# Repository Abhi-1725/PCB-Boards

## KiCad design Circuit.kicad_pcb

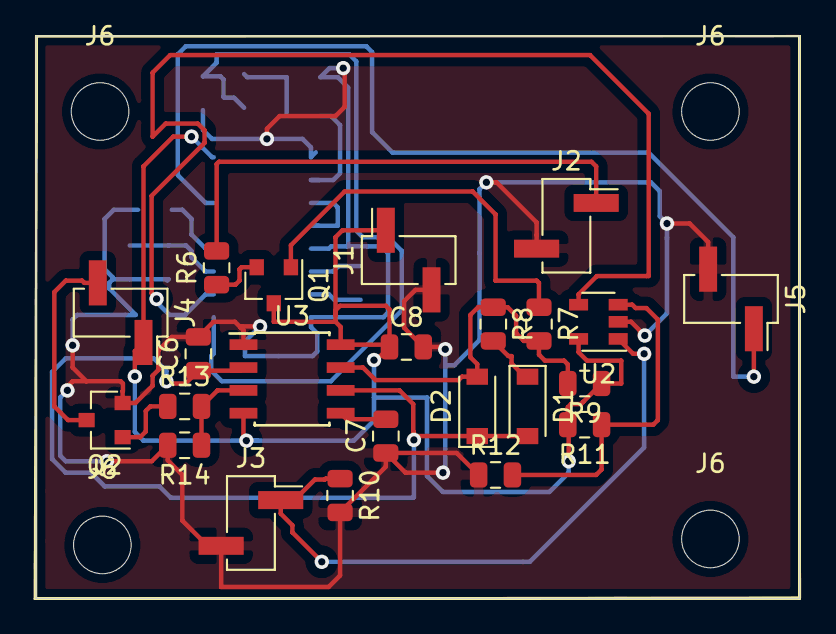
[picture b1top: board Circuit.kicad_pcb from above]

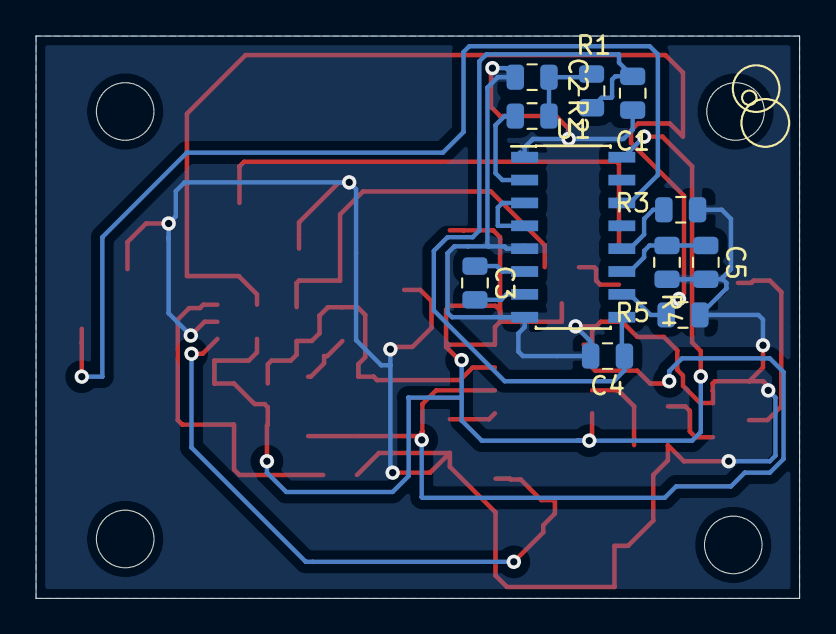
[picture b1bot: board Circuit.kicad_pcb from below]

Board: 2 copper layers, 42.4 x 31.2 mm, 38 parts (11 on the bottom side), 25 nets.

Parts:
C1: 100nF; C_0805_2012Metric
C2: 10nF; C_0805_2012Metric
C3: 22nF; C_0805_2012Metric
C4: 4.7nF; C_0805_2012Metric
C5: 2.2nF; C_0805_2012Metric
C6: 15nF; C_0805_2012Metric
C7: 1nF; C_0805_2012Metric
C8: 2200uF; C_0805_2012Metric
D1, D2: D; D_SOD-123
J1, J2, J3, J4, J5: T; PinHeader_1x02_P2.54mm_Vertical_SMD_Pin1Right
J6, J6#2, J6#3, J6#4: Conn_01x01_Male; MountingHole_3.2mm_M3
Q1: BC327; SOT-23
Q2: 2N7002E; SOT-23
R1, R2, R8: 1K; R_0805_2012Metric
R3, R4: 15K; R_0805_2012Metric
R5, R10: 560; R_0805_2012Metric
R6: R; R_0805_2012Metric
R7: 2K; R_0805_2012Metric
R9: 1.8K; R_0805_2012Metric
R11: 85.3K; R_0805_2012Metric
R12: 12.3K; R_0805_2012Metric
R13: 20; R_0805_2012Metric
R14: 100K; R_0805_2012Metric
U1: 4046; SOIC-16_3.9x9.9mm_P1.27mm
U2: TS881xLx; SOT-23-5
U3: NE555; SOIC-8_3.9x4.9mm_P1.27mm

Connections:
GND: C1.2, C2.2, C4.2, C5.2, C6.2, C7.1, C8.2, J1.2, J2.2, J3.2, J5.2, Q2.2, R3.1, R4.1, R5.1, R10.2, R12.1, R14.2, U1.1, U1.5, U1.8, U2.2, U3.1
unnamed: C1.1, C4.1, R1.1, U1.9
unnamed: C2.1, R1.2, R2.2
unnamed: C3.1, U1.6
unnamed: C3.2, U1.7
unnamed: C5.1, R4.2, U1.11
unnamed: C6.1, D1.2, D2.1, U3.2, U3.6
unnamed: C7.2, U3.5
unnamed: C8.1, J1.1, J4.1, Q1.3, R9.1, R11.2, U1.16, U2.5, U3.4, U3.8
unnamed: D1.1, R8.2
unnamed: D2.2, R7.2, R8.1, R9.2, U3.7
unnamed: J2.1, R6.2
unnamed: J3.1, R10.1, U2.1
unnamed: J4.2, Q2.3
unnamed: J5.1, U1.14
unnamed: J6.1, J6#3.1, J6#4.1
unnamed: Q1.1, R7.1
unnamed: Q1.2, R6.1
unnamed: Q2.1, R13.1
unnamed: R2.1, U1.2
unnamed: R3.2, U1.12
unnamed: R5.2, U1.10, U2.4
unnamed: R11.1, R12.2, U2.3
unnamed: R13.2, R14.1, U3.3
unnamed: U1.3, U1.4
